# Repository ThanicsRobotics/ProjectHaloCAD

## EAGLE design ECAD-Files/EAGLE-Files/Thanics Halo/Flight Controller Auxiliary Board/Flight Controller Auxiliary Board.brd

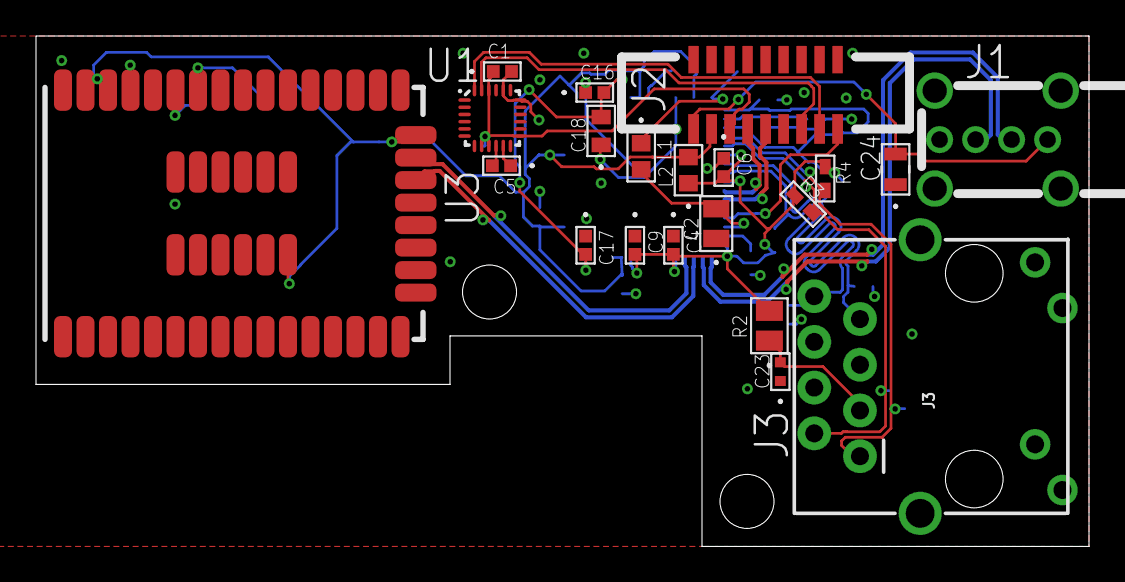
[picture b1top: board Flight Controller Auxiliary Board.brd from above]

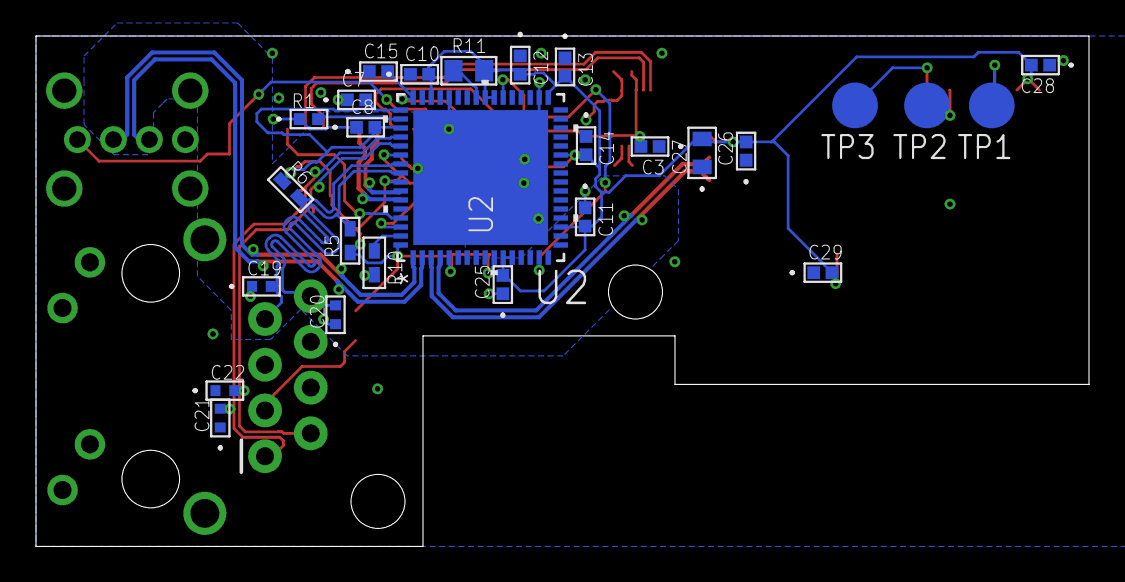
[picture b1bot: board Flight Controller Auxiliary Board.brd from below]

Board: 4 copper layers, 58.5 x 28.4 mm, 48 parts (27 on the bottom side), 29 nets.

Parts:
C1, C3, C4, C5, C6, C7, C8, C9, C10, C11, C12, C13, C14, C15, C16, C17, C25, C26, C28, C29: 0.1uF; 0402-M
C2: 1uF; YAG_CC0805
C18, C27: 4.7uF; 0603-M
C19, C20, C21, C22: 16pF; G-155-M
C23: 22nF; G-155-M
C24: 22uF; G-21
J1: USB_A_VERTICAL
J2: 9POS_FFC_CONNECTOR
J3: MAGJACK
L1, L2: FB; IND_BLM18_0603-M
R1: 12.4k; YAG_R0402-M
R2: 10R; STA_RNCP0805-M
R3, R4, R5, R6: 49R9; RC0402N-M
R10: 12k; RC0402N-M
R11: 10k; RC0805N
TP1, TP2, TP3: TPB2,54; B2,54
U1: QFN40P300X300X105-25N
U2: QFN64_9X9MC-M
U3: WGM110A

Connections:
1.8V: C1.1, C3.2, J2.3, U1.8, U1.9, U1.13, U1.22
3.3V_A: C4.2, C6.2, C7.2, C8.2, C9.2, L2.1, R2.2, R3.1, R4.1, R5.1, R6.1, U2.5, U2.10, U2.49, U2.51, U2.54, U2.57, U2.64
+3V3: C10.2, C11.2, C12.2, C13.2, C14.2, C25.2, C26.2, C27.2, C28.2, C29.2, J2.2, L2.2, R11.2, U2.11, U2.12, U2.19, U2.27, U2.33, U2.39, U2.40, U2.46, U3.24, U3.38, U3.39, U3.51
+5V: C24.2, J1.1, J2.1
GND: C1.2, C2.1, C3.1, C4.1, C5.1, C6.1, C7.1, C8.1, C9.1, C10.1, C11.1, C12.1, C13.1, C14.1, C15.1, C16.1, C17.1, C18.1, C19.1, C20.1, C21.1, C22.1, C23.1, C24.1, C25.1, C26.1, C27.1, C28.1, C29.1, J1.4, J1.P$5, J1.P$6, J1.P$7, J1.P$8, J2.6, J3.10, J3.12, J3.M1, J3.M2, R1.1, R10.2, U1.11, U1.18, U1.20, U2.34, U2.44, U2.65, U3.1, U3.16, U3.25, U3.40, U3.42, U3.44, U3.46, U3.48
GPCLK: J2.9, U2.61
unnamed: R11.1, U2.41
unnamed: R10.1, U2.63
unnamed: C15.2, L1.1, U2.48
unnamed: C2.2, L1.2, U2.62
unnamed: TP1.TP, U3.37
unnamed: TP2.TP, U3.35
unnamed: TP3.TP, U3.34
unnamed: C5.2, U1.10
unnamed: R1.2, U2.50
unnamed: C16.2, C17.2, C18.2, U2.15, U2.38
unnamed: C23.2, J3.3, R2.1
RX_N: C22.2, J3.2, R3.2, U2.53
RX_P: C21.2, J3.1, R4.2, U2.52
SCL: J2.7, U1.23
SDA: J2.8, U1.24
TX_N: C20.2, J3.8, R5.2, U2.56
TX_P: C19.2, J3.7, R6.2, U2.55
USB_D2_N: J1.2, U2.1
USB_D2_P: J1.3, U2.2
USB_D3_N: U2.3, U3.22
USB_D3_P: U2.4, U3.23
USB_D_N: J2.4, U2.58
USB_D_P: J2.5, U2.59

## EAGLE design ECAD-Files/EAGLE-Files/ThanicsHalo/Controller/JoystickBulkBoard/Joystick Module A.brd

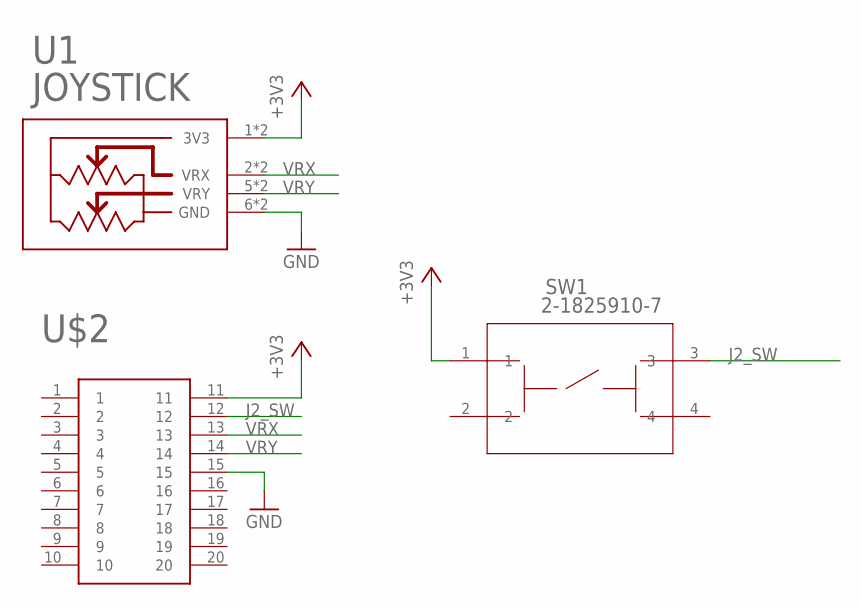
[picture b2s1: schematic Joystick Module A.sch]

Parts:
SW1: 2-1825910-7; SW4_1825910-G
U1: 27800-JOYSTICK
U$2: EDGE_CONNECTOR_20POS_CONTACTS

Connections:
+3V3: SW1.1, U1.1 (3V3), U1.3 (3V3), U$2.11
GND: U1.6 (GND), U1.8 (GND), U$2.15
J2_SW: SW1.3, U$2.12
VRX: U1.2 (VRX), U1.4 (VRX), U$2.13
VRY: U1.5 (VRY), U1.7 (VRY), U$2.14

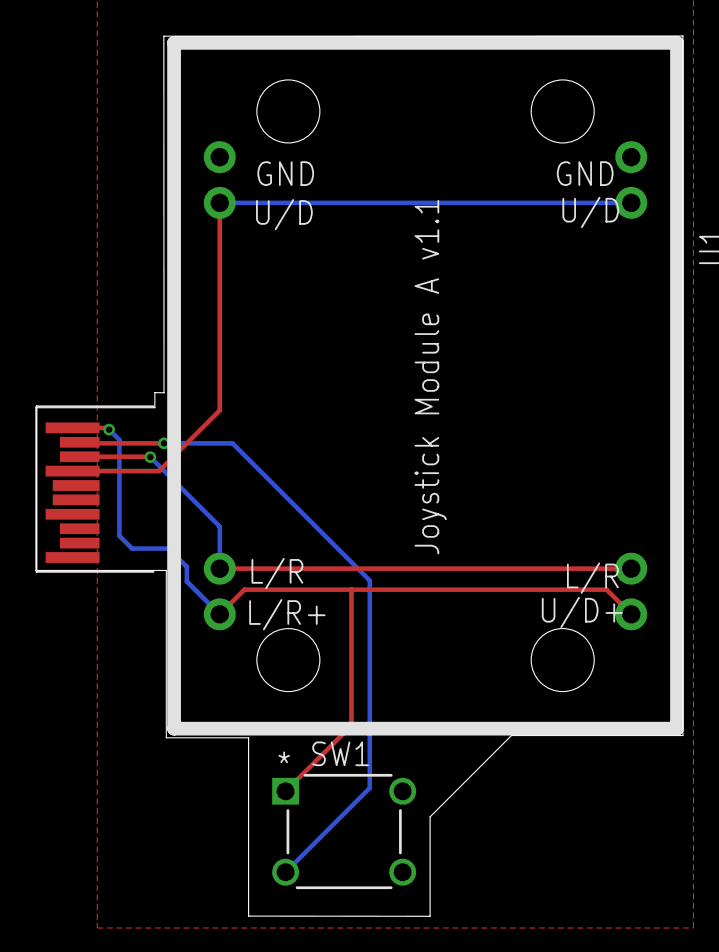
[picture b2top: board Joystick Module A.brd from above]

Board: 2 copper layers, 35.9 x 48.9 mm, 3 parts (0 on the bottom side), 5 nets.

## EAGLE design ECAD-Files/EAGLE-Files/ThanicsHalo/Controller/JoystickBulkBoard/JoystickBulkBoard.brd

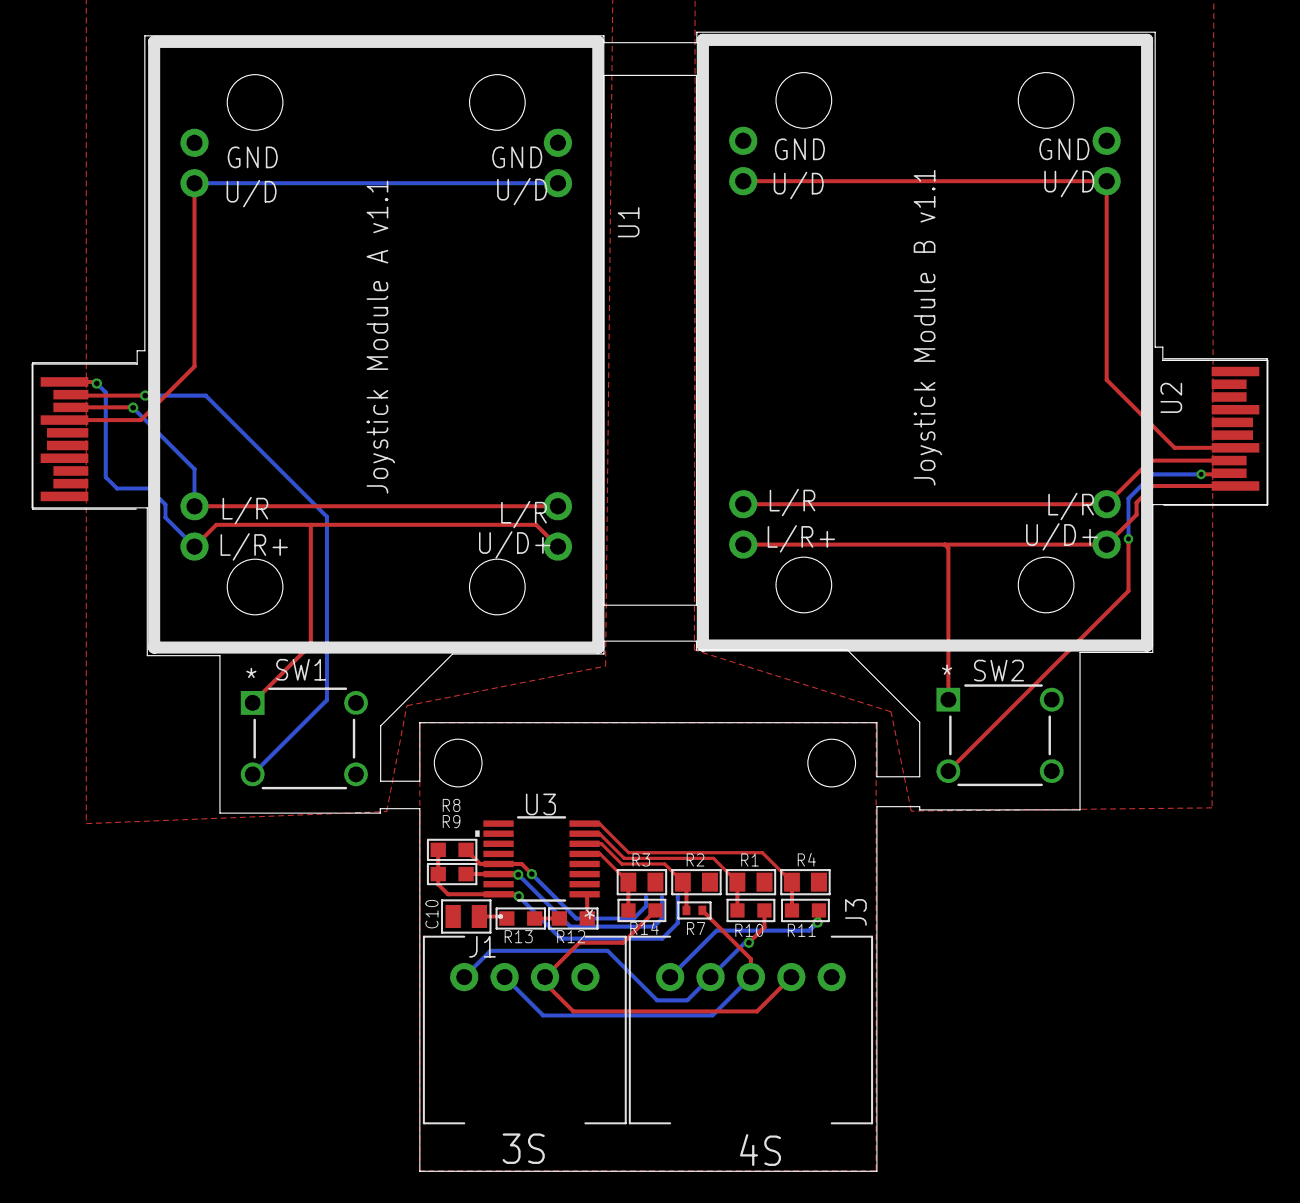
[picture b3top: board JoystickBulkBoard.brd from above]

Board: 2 copper layers, 77.7 x 71.7 mm, 23 parts (1 on the bottom side), 25 nets.

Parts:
C10: 0.1uF; 0805
J1: JST-XH_4POS
J2: JST_SH_4POS
J3: JST-XH_5POS
R1, R2, R3, R4: 10k 0.1%; RC0805N
R7: 15.6k; R0402
R8, R9, R12, R13: 1k; RC0603N-M
R10: 28.4k; R0603
R11: 41.2k; R0603
R14: 2.74k; R0603
SW1, SW2: 2-1825910-7; SW4_1825910-G
U1, U2: 27800-JOYSTICK
U3: MAX11608EEE+21-0055H_16-M; 21-0055H_16-M
U$1, U$2: EDGE_CONNECTOR_20POS_CONTACTS

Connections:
+3V1: SW2.1, U2.1, U2.3, U$1.11
+3V2: J2.1, R8.1, R9.1, U3.16
+3V3: SW1.1, U1.1, U1.3, U$2.11
C1: R3.2, R14.1, U3.5
C2: R2.2, R7.1, U3.6
C3: R1.2, R10.1, U3.7
C4: R4.2, R11.1, U3.8
GND: U1.6, U1.8, U$2.15
GND1: U2.6, U2.8, U$1.15
GND2: C10.2, J1.4, J2.4, J3.5, R1.1, R2.1, R3.1, R4.1, U3.15
I2C_SCL: J2.3, R8.2, U3.13
I2C_SDA: J2.2, R9.2, U3.14
J2_SW: SW1.3, U$2.12
J2_SW1: SW2.3, U$1.12
unnamed: R12.1, U3.1
unnamed: J1.3, J3.4, R14.2
unnamed: J1.2, J3.3, R7.2
unnamed: J1.1, J3.2, R10.2
unnamed: J3.1, R11.2
unnamed: R12.2, R13.1
unnamed: C10.1, R13.2
VRX: U1.2, U1.4, U$2.13
VRX1: U2.2, U2.4, U$1.13
VRY: U1.5, U1.7, U$2.14
VRY1: U2.5, U2.7, U$1.14

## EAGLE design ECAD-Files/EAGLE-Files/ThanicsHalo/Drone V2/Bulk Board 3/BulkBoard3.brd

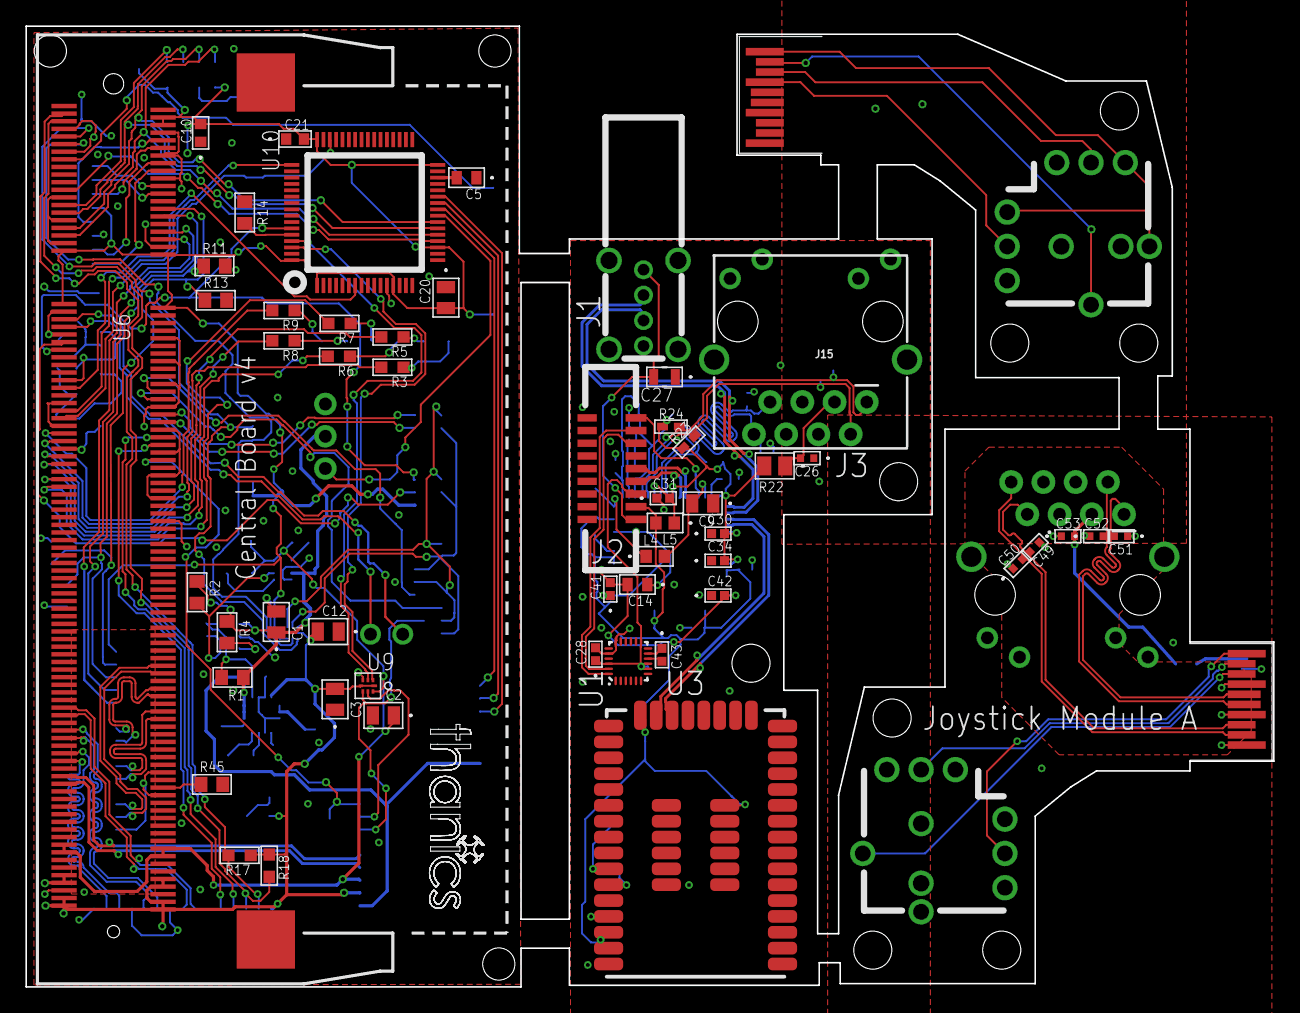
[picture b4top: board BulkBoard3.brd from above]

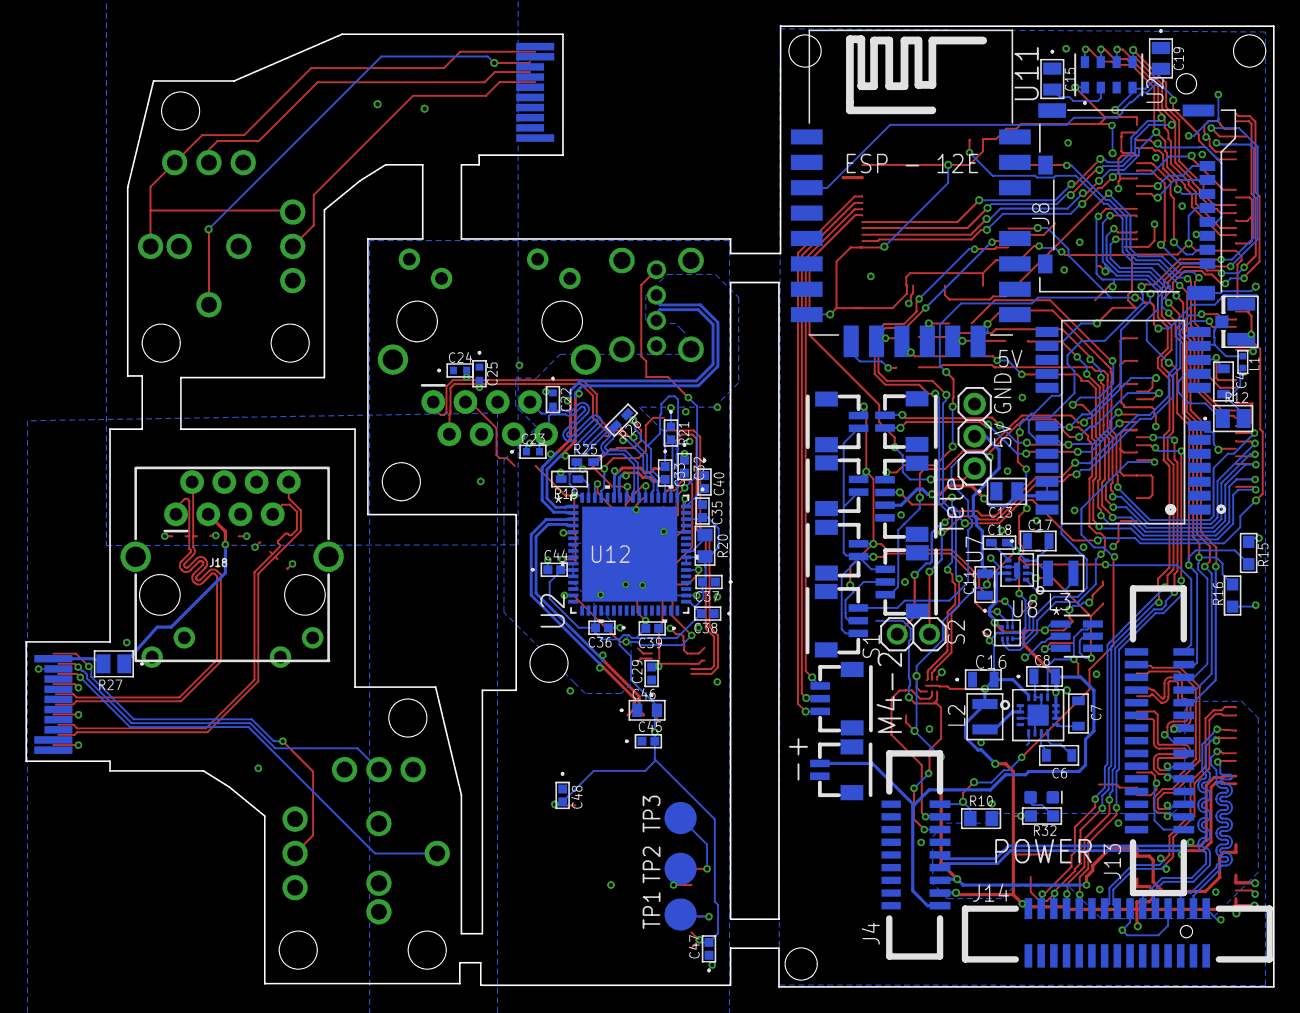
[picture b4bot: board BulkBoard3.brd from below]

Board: 4 copper layers, 98.3 x 75.7 mm, 128 parts (72 on the bottom side), 136 nets.

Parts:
C1, C2, C3, C12, C13, C20: 0.1uF; 0805
C4, C6, C7: 10nF; 0603_CAPACITOR
C5, C14, C46: 4.7uF; 0603-M
C8, C11, C17: 10uF; G-21
C9, C15, C19: 1uF; YAG_CC0805
C10, C21: 2.2uF; G-188-M
C16, C27: 22uF; G-21
C18: 560pF; CC0402N-M
C22, C23, C24, C25, C49, C50, C51, C52: 16pF; G-155-M
C26, C53: 22nF; G-155-M
C28, C29, C30, C31, C32, C33, C34, C35, C36, C37, C38, C39, C40, C41, C42, C43, C44, C45, C47, C48: 0.1uF; 0402-M
D1: GREEN; LED-0603
J1, J2, J6, J7, J9: JST_SH_2POS
J3: JST_SH_4POS
J4, J17: 9POS_FFC_CONNECTOR
J5: U.FL
J8: MICROSD
J10, J11, J12: JST_SH_3POS
J13, J14: 15POS_FFC_CONNECTOR
J15, J18: MAGJACK
J16: USB_A_VERTICAL
JP1: 1X02
JP2: 1X03
L1: 27 nH; 0402_INDUCTOR
L2, L3: 470nH; 1008_INDUCTOR
L4, L5: FB; IND_BLM18_0603-M
R1, R2, R4, R10, R11, R13, R14, R20, R45: 10k; RC0805N
R3, R5, R6, R7, R8, R9, R32: 20R; RC0603N-M
R12: 10; STA_RNCP0805-M
R15, R16, R17, R18: 1k; RC0603N-M
R19: 12k; RC0402N-M
R21: 12.4k; YAG_R0402-M
R22, R27: 10R; STA_RNCP0805-M
R23, R24, R25, R26: 49R9; RC0402N-M
TP1, TP2, TP3: TPB2,54; B2,54
U1: QFN40P300X300X105-25N
U2: LGA8-M
U3: LM3880MF-1AA/NOPBMF06A-M; MF06A-M
U4: NEO-M8
U5: TPS6209; VQFN16
U6: SO-DIMM
U7: MIC23050; MLF(ML)_8PIN
U8, U9: 8-UMLP
U10: LQFP64
U11: ESP12E-SMD
U12: QFN64_9X9MC-M
U13: WGM110A
U$1, U$3: JOYSTICK"; JOYSTICK
U$2, U$4: EDGE_CONNECTOR_20POS_CONTACTS

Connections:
1.8V: C2.1, C17.2, C18.2, J4.3, L3.P$2, U6.183, U6.184, U6.185, U6.186, U7.4, U9.8
1.8V1: C28.1, C29.2, J17.3, U1.8, U1.9, U1.13, U1.22
3.3V_A: C30.2, C31.2, C32.2, C33.2, C34.2, L5.1, R22.2, R23.1, R24.1, R25.1, R26.1, U12.5, U12.10, U12.49, U12.51, U12.54, U12.57, U12.64
3.3V_A1: R27.2, U$2.1
+3V1: C35.2, C36.2, C37.2, C38.2, C39.2, C44.2, C45.2, C46.2, C47.2, C48.2, J17.2, L5.2, R20.2, U12.11, U12.12, U12.19, U12.27, U12.33, U12.39, U12.40, U12.46, U13.24, U13.38, U13.39, U13.51
+3V2: U$1.1, U$1.1', U$1.A, U$2.2
+3V3: C3.2, C10.2, C12.2, C13.2, C16.2, C19.2, C20.2, C21.2, J3.3, J4.2, J8.4, J13.15, J14.15, L2.P$2, R15.1, R16.1, R17.1, R18.1, R32.2, U2.1, U2.4, U4.22, U4.23, U5.16, U6.4, U6.6, U6.39, U6.40, U6.41, U6.42, U6.191, U6.192, U6.193, U6.194, U6.197, U6.198, U6.199, U6.200, U8.1, U8.5, U9.1, U9.5, U10.1, U10.13, U10.19, U10.32, U10.48, U10.64, U11.VCC
+3V4: U$3.1, U$3.1', U$3.A, U$4.11
+5V: C1.1, C8.2, C11.2, J4.1, J6.1, JP2.2, R1.1, R2.1, R4.1, U3.1, U5.10, U5.11, U5.12, U7.7, U8.8
+5V1: C27.2, J16.1, J17.1
C0_C_N: J13.8, U6.144
C0_C_P: J13.9, U6.142
C0_D0_N: J13.2, U6.138
C0_D0_P: J13.3, U6.136
C0_D1_N: J13.5, U6.150
C0_D1_P: J13.6, U6.148
C0_IO0: J13.11, U6.36
C0_IO1: J13.12, U6.34
C1_C_N: J14.8, U6.149
C1_C_P: J14.9, U6.147
C1_D0_N: J14.2, U6.161
C1_D0_P: J14.3, U6.159
C1_D1_N: J14.5, U6.155
C1_D1_P: J14.6, U6.153
C1_IO0: J14.11, U6.78
C1_IO1: J14.12, U6.76
GND: C1.2, C2.2, C3.1, C4.1, C5.1, C7.1, C8.1, C10.1, C11.1, C12.1, C13.1, C15.1, C16.1, C17.1, C19.1, C20.1, C21.1, D1.C, J3.4, J4.6, J5.P$1, J5.P$2, J6.2, J8.6, J8.9, J8.10, J8.11, J8.12, J8.13, J13.1, J13.4, J13.7, J13.10, J14.1, J14.4, J14.7, J14.10, JP2.3, R10.2, R11.2, R13.2, R14.1, R45.2, U2.3, U3.2, U4.7, U4.10, U4.12, U4.13, U4.24, U5.3, U5.5, U5.6, U5.14, U5.15, U5.17, U6.1, U6.7, U6.8, U6.13, U6.14, U6.19, U6.20, U6.25, U6.26, U6.31, U6.32, U6.37, U6.38, U6.43, U6.44, U6.49, U6.50, U6.55, U6.56, U6.61, U6.62, U6.67, U6.68, U6.73, U6.74, U6.79, U6.80, U6.85, U6.86, U6.91, U6.92, U6.97, U6.98, U6.103, U6.104, U6.109, U6.110, U6.115, U6.116, U6.121, U6.122, U6.127, U6.133, U6.134, U6.139, U6.140, U6.145, U6.146, U6.151, U6.152, U6.157, U6.163, U6.164, U6.169, U6.170, U6.181, U6.182, U6.187, U6.188, U6.195, U6.196, U6.G1, U6.G2, U7.6, U7.8, U7.EP, U8.4, U9.4, U10.12, U10.18, U10.31, U10.47, U10.63, U11.GND
GND1: C9.1, C14.1, C22.1, C23.1, C24.1, C25.1, C26.1, C27.1, C28.2, C29.1, C30.1, C31.1, C32.1, C33.1, C34.1, C35.1, C36.1, C37.1, C38.1, C39.1, C40.1, C41.1, C42.1, C43.1, C44.1, C45.1, C46.1, C47.1, C48.1, J15.10, J15.12, J15.M1, J15.M2, J16.4, J16.P$5, J16.P$6, J16.P$7, J16.P$8, J17.6, R19.2, R21.1, U1.11, U1.18, U1.20, U12.34, U12.44, U12.65, U13.1, U13.16, U13.25, U13.40, U13.42, U13.44, U13.46, U13.48
GND2: C49.1, C50.1, C51.1, C52.1, C53.1, J18.10, J18.12, J18.M1, J18.M2, U$1.3, U$1.3', U$2.11, U$2.14, U$2.17
GND3: U$3.3, U$3.3', U$4.15
GPCLK: J17.9, U12.61
GPCLK1: J4.9, R10.1, U6.82
I2C_MPU_SCL: U9.3, U10.61
I2C_MPU_SDA: U9.2, U10.62
I2C_SCL: U4.19, U6.11, U8.3
I2C_SCL_1V8: J4.7, U9.6
I2C_SCL_5V: J1.2, J2.2, J7.2, J10.2, J11.2, U8.6
I2C_SDA: U4.18, U6.9, U8.2
I2C_SDA_1V8: J4.8, U9.7
I2C_SDA_5V: J1.1, J2.1, J7.1, J10.1, J11.1, U8.7
ID_SD: U6.15, U11.CH_PD
INT_A: J10.3, U6.64
INT_B: J11.3, U6.66
J2_SW: U$1.B, U$2.18
J2_SW1: U$3.B, U$4.12
MOTOR1: JP2.1, U10.24
MOTOR2: J12.1, U10.25
MOTOR3: J12.2, U10.26
MOTOR4: J12.3, U10.27
unnamed: J5.P$3, L1.P$1, U4.11
unnamed: C6.2, U5.7
unnamed: C6.1, U5.8
unnamed: D1.A, R32.1
unnamed: R1.2, U3.6, U5.13
unnamed: R2.2, U3.5, U7.2
unnamed: R3.1, U11.CS0
unnamed: R5.1, U11.MISO
unnamed: R6.1, U11.GPIO9
unnamed: R7.1, U11.GPIO10
unnamed: C5.2, U10.30
unnamed: C15.2, U2.2
unnamed: R12.1, U4.9
unnamed: R8.1, U11.MOSI
unnamed: R9.1, U11.SCLK
unnamed: R14.2, U10.60
unnamed: C43.2, U1.10
unnamed: R20.1, U12.41
unnamed: R19.1, U12.63
unnamed: TP1.TP, U13.37
unnamed: TP2.TP, U13.35
unnamed: TP3.TP, U13.34
unnamed: C4.2, L1.P$2, R12.2
unnamed: C40.2, L4.1, U12.48
unnamed: C7.2, U5.9
unnamed: L2.P$1, U5.1, U5.2
unnamed: C9.2, L4.2, U12.62
unnamed: L3.P$1, U7.1
unnamed: R21.2, U12.50
unnamed: C14.2, C41.2, C42.2, U12.15, U12.38
unnamed: C26.2, J15.3, R22.1
unnamed: C53.2, J18.3, R27.1
unnamed: C18.1, U7.5
unnamed: R45.1, U6.168
NRST: U6.63, U10.7
POWER_SEQ_EN: R4.2, U3.3
RX_N: C25.2, J15.2, R23.2, U12.53
RX_N1: C52.2, J18.2, U$2.15
RX_P: C24.2, J15.1, R24.2, U12.52
RX_P1: C51.2, J18.1, U$2.16
SCL: J17.7, U1.23
SCL0: J13.13, R11.1, R16.2, U6.30
SCL1: J14.13, R18.2, U6.5
SDA: J17.8, U1.24
SDA0: J13.14, R13.1, R15.2, U6.28
SDA1: J14.14, R17.2, U6.3
SDX_CLK: J8.5, U6.10
SDX_CMD: J8.3, U6.12
SDX_D0: J8.7, U6.16
SDX_D1: J8.8, U6.18
SDX_D2: J8.1, U6.22
SDX_D3: J8.2, U6.24
SD_CLK: R9.2, U6.75
SD_CMD: R3.2, U6.77
SD_D0: R5.2, U6.81
SD_D1: R8.2, U6.83
SD_D2: R6.2, U6.87
SD_D3: R7.2, U6.89
SERVO1: JP1.1, U6.45
SERVO2: JP1.2, U6.47
SPI_CS0: U2.5, U6.27
SPI_CS1: U6.23, U10.20
SPI_MISO: U2.6, U6.29, U10.22
SPI_MOSI: U2.7, U6.33, U10.23
SPI_SCLK: U2.8, U6.35, U10.21
SWCLK: U6.69, U10.49
SWDIO: U6.71, U10.46
TX_N: C23.2, J15.8, R25.2, U12.56
TX_N1: C50.2, J18.8, U$2.12
TX_P: C22.2, J15.7, R26.2, U12.55
TX_P1: C49.2, J18.7, U$2.13
UART2_RX: J9.2, U6.72
UART2_TX: J9.1, U6.70
USART1_RX: J3.1, U6.53, U10.59
USART1_TX: J3.2, U6.51
USB_D2_N: J16.2, U12.1
USB_D2_P: J16.3, U12.2
USB_D3_N: U12.3, U13.22
USB_D3_P: U12.4, U13.23
USB_D_N: J4.4, U6.167
USB_D_N1: J17.4, U12.58
USB_D_P: J4.5, U6.165
USB_D_P1: J17.5, U12.59
VRX: U$1.2, U$2.20
VRX1: U$3.2, U$4.13
VRY: U$1.2', U$2.19
VRY1: U$3.2', U$4.14

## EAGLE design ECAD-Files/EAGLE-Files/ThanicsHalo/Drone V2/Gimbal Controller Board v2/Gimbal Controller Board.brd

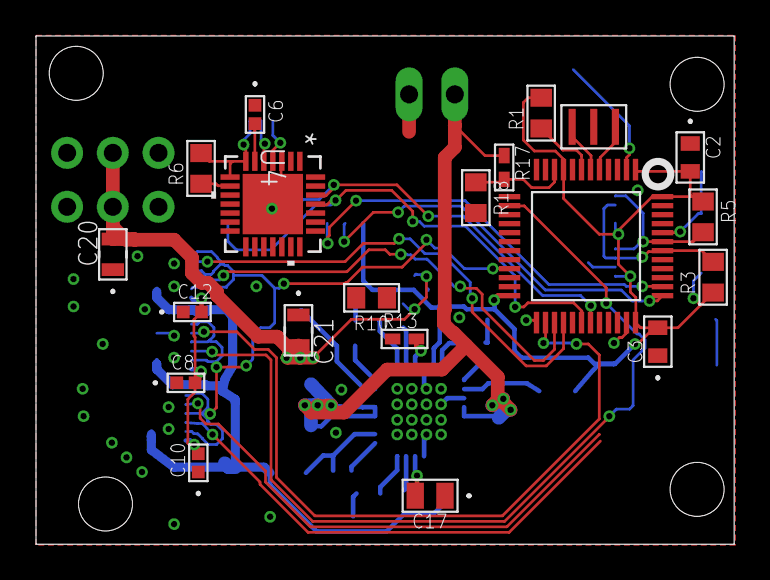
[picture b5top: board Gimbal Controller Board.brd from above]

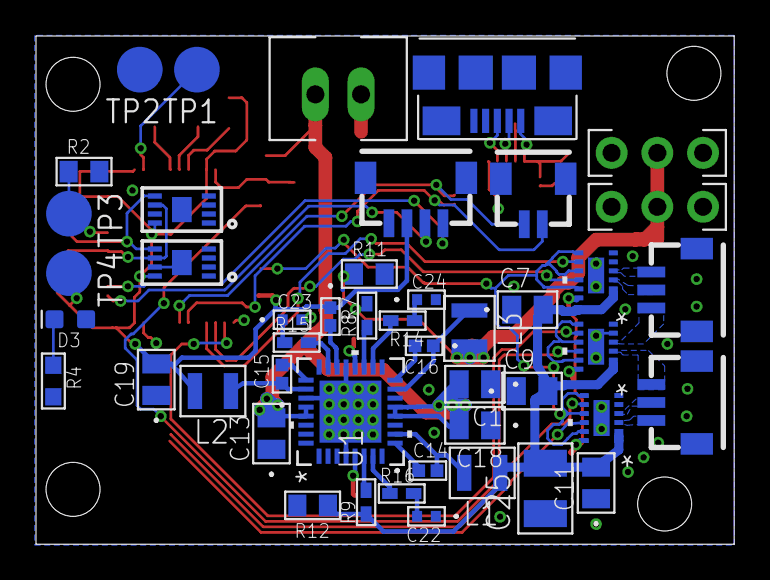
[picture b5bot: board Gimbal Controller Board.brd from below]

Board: 2 copper layers, 38.8 x 28.2 mm, 66 parts (46 on the bottom side), 54 nets.

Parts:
C1, C7, C9, C11, C13, C18, C19: 10uF; 0805_CAPACITOR
C2, C3: 4.7uF; 0603-M
C6, C8, C10, C12, C14, C15, C16: 0.1uF; 0402-M
C17: 1uF; YAG_CC0805
C20, C21: 22uF; G-21
C22, C23, C24: 2.2nF; 0402_CAPACITOR
C25: 100uF; 1210_CAPACITOR
D3: GREEN; LED-0603
J1, J2: JST_SH_3POS
J3: GIMBAL_POWER_CONNECTOR; XH_CONNECTOR
J4, J5: SERVO_CONNECTOR
J6: JST_SH_2POS
J7: JST_SH_4POS
J8: USB_MICRO_B_SMT
L1, L2, L3: 4.7uH; 1008
R1, R2, R3, R5, R6, R10, R11, R12, R18: 10k; RC0805N
R4: 1k; RC0603N-M
R7: 45.3k; STA_RMCF0402-M
R8, R13: 73.2k; RC0402N-M
R9: 158k; RC0402N-M
R14, R15, R16: 20k; RC0402N-M
R17: 68k; RC0402N-M
TP1, TP2, TP3, TP4: TPB2,54; B2,54
U1: TPS65261RHBR; RHB32_3P45X3P45
U2, U5, U6: DRV8839DSSR; DSS12_P9X2
U4: CP2102-GMRQFN28_5X5-M; QFN28_5X5-M
U7: STM32F303; LQFP48
U8: ATSHA204A; UDFN8_3X2
U9: CAT24C256; UDFN8_3X2
X1: 3-SMD

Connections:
+3V3: C2.2, C3.2, C8.2, C10.2, C12.2, C19.2, J7.2, L2.P$2, R1.2, R3.1, R5.1, R7.1, R10.1, TP4.TP, U2.12, U5.12, U6.12, U7.1, U7.9, U7.24, U7.36, U7.48, U8.8, U9.8
+5V: C20.2, C21.2, J4.2, J5.2, L3.P$2, R8.2, R11.1
+10V: C7.2, C9.2, C11.2, C25.2, L1.P$1, R9.1, R12.1, U2.1, U2.2, U5.1, U5.2, U6.1, U6.2
BTN: TP1.TP, U7.2
EN_MOTOR: U2.7, U2.9, U2.11, U5.7, U5.9, U5.11, U6.7, U6.9, U6.11, U7.21
GND: C1.1, C2.1, C3.1, C6.1, C7.1, C8.1, C9.1, C10.1, C11.1, C12.1, C13.1, C17.1, C18.1, C19.1, C20.1, C21.1, C22.1, C23.2, C24.2, C25.1, J3.2, J4.3, J5.3, J7.1, J8.5, J8.6, J8.7, J8.P$1, J8.P$2, J8.P$3, J8.P$4, R2.2, R4.2, R10.2, R11.2, R12.2, R13.1, R18.2, TP2.TP, U1.4, U1.11, U1.14, U1.21, U1.27, U1.33, U2.5, U2.6, U2.13, U4.3, U4.29, U5.5, U5.6, U5.13, U6.5, U6.6, U6.13, U7.8, U7.23, U7.35, U7.47, U8.4, U9.1, U9.2, U9.3, U9.4, U9.7, U9.9, X1.2
I2C1_SCL: J7.4, U7.38
I2C1_SDA: J7.3, U7.37
I2C2_SCL: R3.2, U7.42, U8.6, U9.6
I2C2_SDA: R5.2, U7.43, U8.5, U9.5
LED: D3.A, U7.25
unnamed: C16.2, U1.16
unnamed: U7.5, X1.3
unnamed: R8.1, U1.19
unnamed: R1.1, U7.7
unnamed: D3.C, R4.1
unnamed: R2.1, TP3.TP, U7.44
unnamed: J8.2, U4.5
unnamed: J8.3, U4.4
unnamed: R6.1, U4.9
unnamed: C6.2, U4.6
unnamed: C14.1, U1.9
unnamed: R14.2, U1.18
unnamed: R9.2, U1.6
unnamed: R13.2, U1.20
unnamed: C15.1, L2.P$1, U1.26
unnamed: C15.2, U1.25
unnamed: R7.2, U1.22
unnamed: C24.1, R14.1
unnamed: C16.1, L3.P$1, U1.15
unnamed: C14.2, L1.P$2, U1.10
unnamed: C17.2, U1.5
unnamed: U7.6, X1.1
unnamed: R16.1, U1.7
unnamed: C22.2, R16.2
unnamed: R15.2, U1.23
unnamed: C23.1, R15.1
P$1: J8.1, R6.2, U4.7, U4.8
PITCH1: J2.3, U6.3
PITCH2: J2.2, U6.4
PITCH3: J2.1, U5.3
ROLL1: J1.3, U5.4
ROLL2: J1.2, U2.3
ROLL3: J1.1, U2.4
TIM1_CH1N: U5.8, U7.26
TIM1_CH2N: U2.10, U7.27
TIM1_CH3N: U2.8, U7.28
TIM3_CH2: U5.10, U7.14
TIM3_CH3: U6.10, U7.18
TIM3_CH4: U6.8, U7.19
USART1_RX: J6.1, U4.26, U7.31
USART1_TX: J6.2, U4.25, U7.30
VCC_MEASURE: R17.2, R18.1, U7.10
V_BATT: C1.2, C13.2, C18.2, J3.1, R17.1, U1.12, U1.13, U1.28, U1.29

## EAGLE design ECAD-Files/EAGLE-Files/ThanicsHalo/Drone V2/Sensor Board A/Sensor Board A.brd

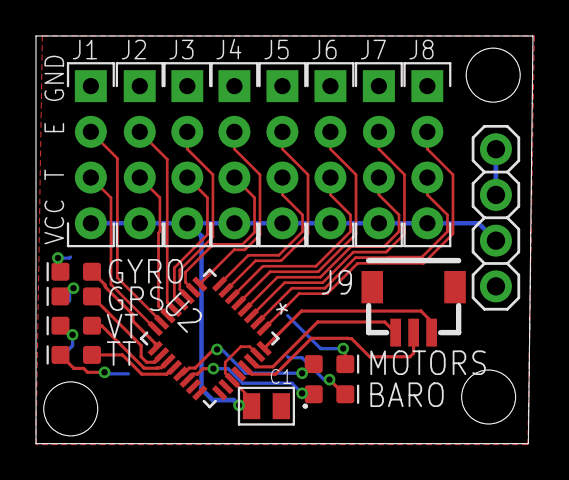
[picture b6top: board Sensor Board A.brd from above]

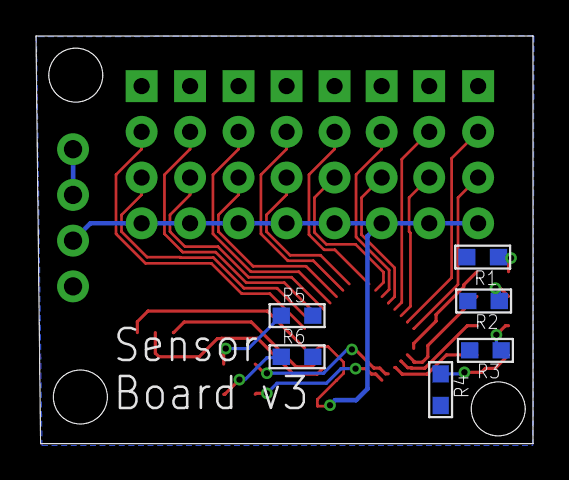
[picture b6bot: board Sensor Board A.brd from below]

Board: 2 copper layers, 27.6 x 22.6 mm, 24 parts (6 on the bottom side), 34 nets.

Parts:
C1: 0.1uF; 0805
D1, D2, D3, D4, D5, D6: LED-0603
J1, J2, J3, J4, J5, J6, J7, J8: HC-SR04; HC-SR04_FOOTPRINT
J9: JST_SH_3POS
JP1: 1X04
R1, R2, R3, R4, R5, R6: 1k; RC0603N-M
U2: TCA6424ARGJRRGJ32-M; RGJ32-M

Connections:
+5V: C1.2, J1.VCC, J2.VCC, J3.VCC, J4.VCC, J5.VCC, J6.VCC, J7.VCC, J8.VCC, JP1.3, U2.27, U2.31
ECHO1: J1.ECHO, U2.15
ECHO2: J2.ECHO, U2.13
ECHO3: J3.ECHO, U2.11
ECHO4: J4.ECHO, U2.9
ECHO5: J5.ECHO, U2.7
ECHO6: J6.ECHO, U2.5
ECHO7: J7.ECHO, U2.3
ECHO8: J8.ECHO, U2.1
GND: C1.1, J1.GND, J2.GND, J3.GND, J4.GND, J5.GND, J6.GND, J7.GND, J8.GND, JP1.4, R1.2, R2.2, R3.2, R4.2, R5.2, R6.2, U2.25, U2.26
INT: J9.3, U2.32
unnamed: JP1.1, JP1.2
unnamed: D1.A, U2.17
unnamed: D2.A, U2.18
unnamed: D3.A, U2.19
unnamed: D4.A, U2.20
unnamed: D5.A, U2.21
unnamed: D6.A, U2.22
unnamed: D6.C, R6.1
unnamed: D5.C, R5.1
unnamed: D4.C, R4.1
unnamed: D3.C, R3.1
unnamed: D2.C, R2.1
unnamed: D1.C, R1.1
SCL: J9.2, U2.29
SDA: J9.1, U2.30
TRIG1: J1.TRIG, U2.16
TRIG2: J2.TRIG, U2.14
TRIG3: J3.TRIG, U2.12
TRIG4: J4.TRIG, U2.10
TRIG5: J5.TRIG, U2.8
TRIG6: J6.TRIG, U2.6
TRIG7: J7.TRIG, U2.4
TRIG8: J8.TRIG, U2.2

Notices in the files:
parts and their libraries:
SparkFun-Connectors: Licensing: Creative Commons ShareAlike 4.0 International - https://creativecommons.org/licenses/by-sa/4.0
COPYRIGHT: Copyright C 2015 Accelerated Designs. All rights reserved
